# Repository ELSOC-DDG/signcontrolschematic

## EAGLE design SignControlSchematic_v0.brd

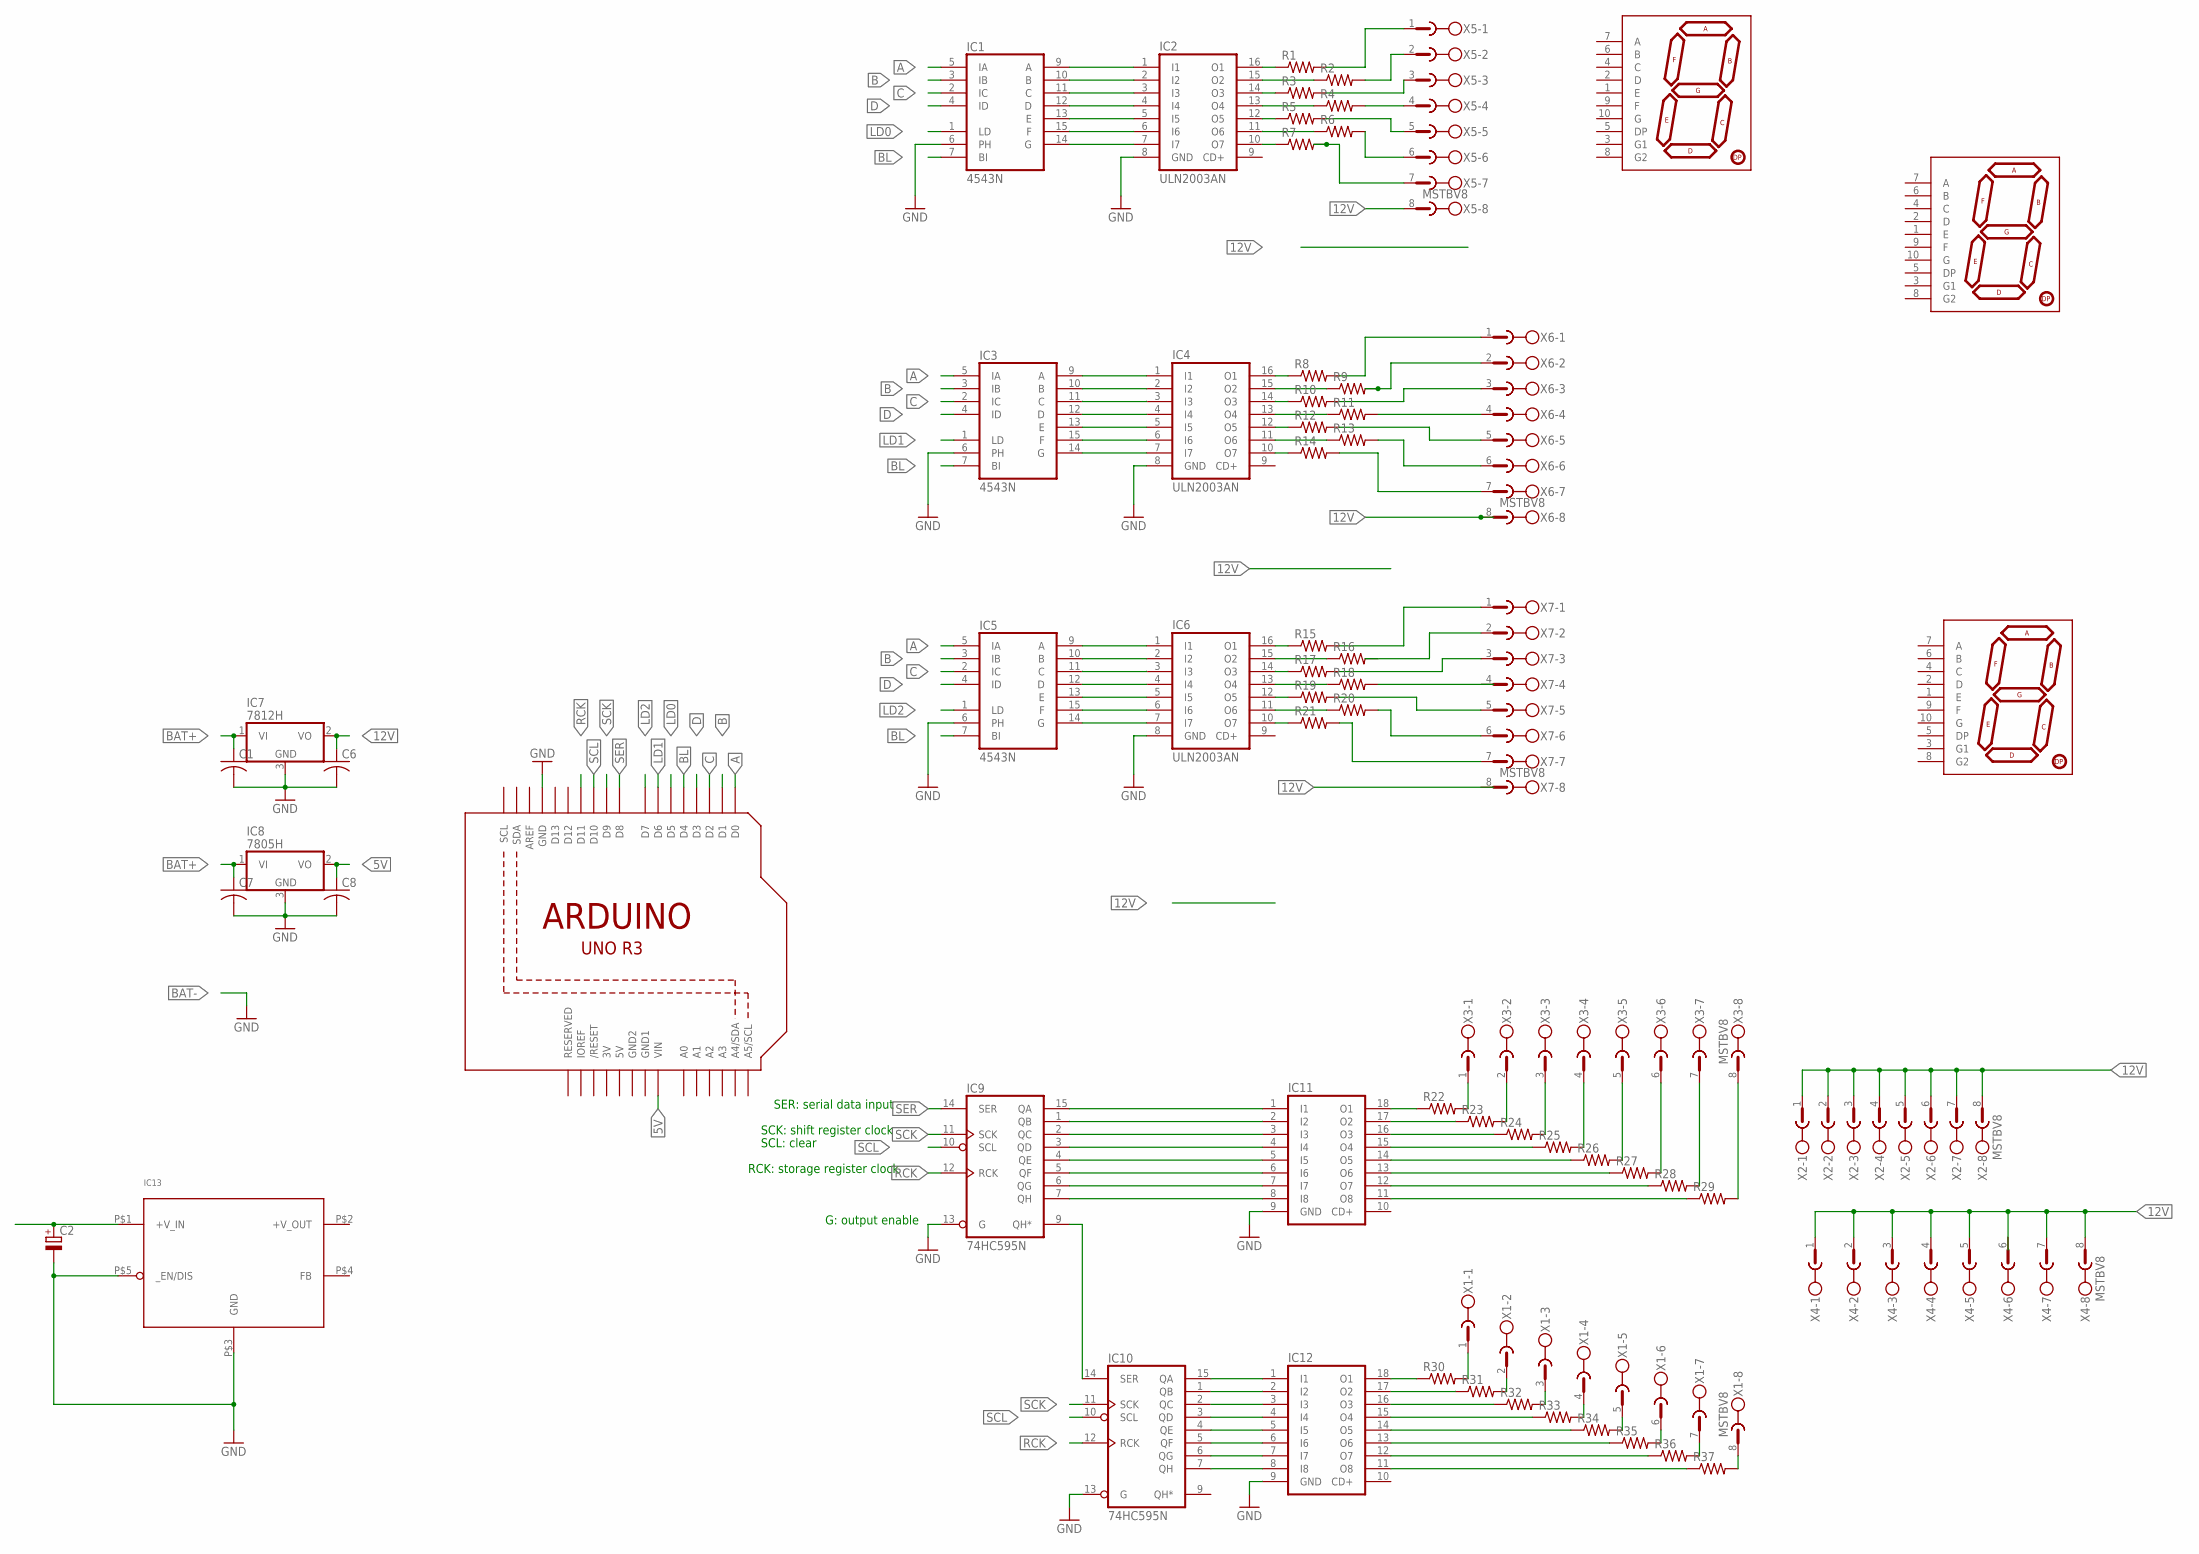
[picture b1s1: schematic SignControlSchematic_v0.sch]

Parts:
C1, C6, C7, C8: C-US025-024X044; C025-024X044
C2: CPOL-EUE7.5-16; E7,5-16
IC1, IC3, IC5: 4543N; DIL16
IC2, IC4, IC6: ULN2003AN; DIL16
IC7: 7812H; TO39
IC8: 7805H; TO39
IC9, IC10: 74HC595N; DIL16
IC11, IC12: ULN2803A; DIL18
IC13: LM2576-T05A; TO-220-5_IN-LINE
R1, R2, R3, R4, R5, R6, R7, R8, R9, R10, R11, R12, R13, R14, R15, R16, R17, R18, R19, R20, R21, R22, R23, R24, R25, R26, R27, R28, R29, R30, R31, R32, R33, R34, R35, R36, R37: R-US_0204/2V; 0204V
U1: ARDUINOR3-BPLACE
U$1, U$2, U$3: 7-SEGMENT-DISPLAY-1"-RED; 7-SEGMENT-1"PTH
X1, X2, X3, X4, X5, X6, X7: MSTBV8

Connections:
3V: U1.3V
5V: C8.1, IC8.2 (VO), U1.5V, U1.VIN
12V: C6.1, IC7.2 (VO), X2.1, X2.2, X2.3, X2.4, X2.5, X2.6, X2.7, X2.8, X4.1, X4.2, X4.3, X4.4, X4.5, X4.7, X4.8, X5.8, X6.8
A: IC1.5 (IA), IC3.5 (IA), IC5.5 (IA), U1.D0
B: IC1.3 (IB), IC3.3 (IB), IC5.3 (IB), U1.D1
BAT+: C1.1, C7.1, IC7.1 (VI), IC8.1 (VI)
BL: IC1.7 (BI), IC3.7 (BI), IC5.7 (BI), U1.D4
C: IC1.2 (IC), IC3.2 (IC), IC5.2 (IC), U1.D2
D: IC1.4 (ID), IC3.4 (ID), IC5.4 (ID), U1.D3
GND: C1.2, C2.-, C6.2, C7.2, C8.2, IC1.6 (PH), IC2.8 (GND), IC3.6 (PH), IC4.8 (GND), IC5.6 (PH), IC6.8 (GND), IC7.3 (GND), IC8.3 (GND), IC9.8 (GND), IC9.13 (G), IC10.8 (GND), IC10.13 (G), IC11.9 (GND), IC12.9 (GND), IC13.P$3 (GND), IC13.P$5 (_EN/DIS), U1.GND
GND1: U1.GND1
GND2: U1.GND2
LD0: IC1.1 (LD), U1.D5
LD1: IC3.1 (LD), U1.D6
LD2: IC5.1 (LD), U1.D7
unnamed: IC1.9 (A), IC2.1 (I1)
unnamed: IC2.16 (O1), R1.1
unnamed: IC1.10 (B), IC2.2 (I2)
unnamed: R1.2, X5.1
unnamed: IC1.11 (C), IC2.3 (I3)
unnamed: IC2.15 (O2), R2.1
unnamed: IC1.12 (D), IC2.4 (I4)
unnamed: R2.2, X5.2
unnamed: IC1.13 (E), IC2.5 (I5)
unnamed: IC2.14 (O3), R3.1
unnamed: IC1.15 (F), IC2.6 (I6)
unnamed: IC1.14 (G), IC2.7 (I7)
unnamed: R3.2, X5.3
unnamed: R4.2, X5.4
unnamed: IC3.9 (A), IC4.1 (I1)
unnamed: IC2.13 (O4), R4.1
unnamed: IC3.10 (B), IC4.2 (I2)
unnamed: IC2.12 (O5), R5.1
unnamed: IC3.11 (C), IC4.3 (I3)
unnamed: R5.2, X5.5
unnamed: IC3.12 (D), IC4.4 (I4)
unnamed: R6.2, X5.6
unnamed: IC3.13 (E), IC4.5 (I5)
unnamed: IC2.11 (O6), R6.1
unnamed: IC3.15 (F), IC4.6 (I6)
unnamed: IC3.14 (G), IC4.7 (I7)
unnamed: IC2.10 (O7), R7.1
unnamed: R7.2, X5.7
unnamed: IC5.9 (A), IC6.1 (I1)
unnamed: IC4.16 (O1), R8.1
unnamed: IC5.10 (B), IC6.2 (I2)
unnamed: R8.2, X6.1
unnamed: IC5.11 (C), IC6.3 (I3)
unnamed: R9.2, X6.2
unnamed: IC5.12 (D), IC6.4 (I4)
unnamed: IC4.15 (O2), R9.1
unnamed: IC5.13 (E), IC6.5 (I5)
unnamed: IC4.14 (O3), R10.1
unnamed: IC5.15 (F), IC6.6 (I6)
unnamed: IC5.14 (G), IC6.7 (I7)
unnamed: R10.2, X6.3
unnamed: R11.2, X6.4
unnamed: IC4.13 (O4), R11.1
unnamed: IC4.12 (O5), R12.1
unnamed: R12.2, X6.5
unnamed: R13.2, X6.6
unnamed: IC4.11 (O6), R13.1
unnamed: IC4.10 (O7), R14.1
unnamed: R14.2, X6.7
unnamed: IC6.16 (O1), R15.1
unnamed: R15.2, X7.1
unnamed: IC6.15 (O2), R16.1
unnamed: IC6.14 (O3), R17.1
unnamed: R17.2, X7.3
unnamed: IC6.13 (O4), R18.1
unnamed: IC6.12 (O5), R19.1
unnamed: R19.2, X7.5
unnamed: R20.2, X7.6
unnamed: IC6.11 (O6), R20.1
unnamed: IC6.10 (O7), R21.1
unnamed: R21.2, X7.7
unnamed: R22.2, X3.1
unnamed: R23.2, X3.2
unnamed: R24.2, X3.3
unnamed: R25.2, X3.4
unnamed: R26.2, X3.5
unnamed: R27.2, X3.6
unnamed: R28.2, X3.7
unnamed: R29.2, X3.8
unnamed: R30.2, X1.1
unnamed: R31.2, X1.2
unnamed: R32.2, X1.3
unnamed: R33.2, X1.4
unnamed: R34.2, X1.5
unnamed: R35.2, X1.6
unnamed: R36.2, X1.7
unnamed: R37.2, X1.8
unnamed: IC11.18 (O1), R22.1
unnamed: IC11.17 (O2), R23.1
unnamed: IC11.16 (O3), R24.1
unnamed: IC11.15 (O4), R25.1
unnamed: IC11.14 (O5), R26.1
unnamed: IC11.13 (O6), R27.1
unnamed: IC11.12 (O7), R28.1
unnamed: IC11.11 (O8), R29.1
unnamed: IC12.18 (O1), R30.1
unnamed: IC12.17 (O2), R31.1
unnamed: IC12.16 (O3), R32.1
unnamed: IC12.15 (O4), R33.1
unnamed: IC12.14 (O5), R34.1
unnamed: IC12.13 (O6), R35.1
unnamed: IC12.12 (O7), R36.1
unnamed: IC12.11 (O8), R37.1
unnamed: IC9.9 (QH*), IC10.14 (SER)
unnamed: IC9.15 (QA), IC11.1 (I1)
unnamed: IC9.1 (QB), IC11.2 (I2)
unnamed: IC9.2 (QC), IC11.3 (I3)
unnamed: IC9.3 (QD), IC11.4 (I4)
unnamed: IC9.4 (QE), IC11.5 (I5)
unnamed: IC9.5 (QF), IC11.6 (I6)
unnamed: IC9.6 (QG), IC11.7 (I7)
unnamed: IC9.7 (QH), IC11.8 (I8)
unnamed: IC10.15 (QA), IC12.1 (I1)
unnamed: IC10.1 (QB), IC12.2 (I2)
unnamed: IC10.2 (QC), IC12.3 (I3)
unnamed: IC10.3 (QD), IC12.4 (I4)
unnamed: IC10.4 (QE), IC12.5 (I5)
unnamed: IC10.5 (QF), IC12.6 (I6)
unnamed: IC10.6 (QG), IC12.7 (I7)
unnamed: IC10.7 (QH), IC12.8 (I8)
unnamed: C2.+, IC13.P$1 (+V_IN)
RCK: IC9.12 (RCK), IC10.12 (RCK), U1.D11
SCK: IC9.11 (SCK), IC10.11 (SCK), U1.D9
SCL: IC9.10 (SCL), IC10.10 (SCL), U1.D10
SER: IC9.14 (SER), U1.D8
VCC: IC9.16 (VCC), IC10.16 (VCC)
VDD: IC1.16 (VDD), IC3.16 (VDD), IC5.16 (VDD)
VSS: IC1.8 (VSS), IC3.8 (VSS), IC5.8 (VSS)

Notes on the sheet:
SER: serial data input
SCK: shift register clock
SCL: clear
RCK: storage register clock
G: output enable

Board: 2 copper layers, 66 parts (0 on the bottom side), 130 nets, no tracks yet.

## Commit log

2017-03-25 Initial commit - from James S-S original schematics, added connectors and in the middle of adding the 5V regulator
2017-04-01 Converted to Altium
2017-04-01 Add __Previews dir to gitignore
2017-04-01 Actually add previews dir to gitignore

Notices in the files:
parts and their libraries:
SparkFun-Displays: Licensing: Creative Commons ShareAlike 4.0 International - https://creativecommons.org/licenses/by-sa/4.0
